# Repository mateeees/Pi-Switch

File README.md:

# Pi-Switch
## About
Pi Switch is a project that turns your Raspberry Pi into multi purpouse on/off switch for your : 
* servers
* computers
* and theoreticaly much more

## Website

https://mateeees.github.io/Pi-Switch/

## How it works?
You SSH to the Pi Switch and using the python script you turn on one of the three LEDs that shine directly to a photoresistor,which lowers its resistance to a minumum,"shorts the circuit" instead of a power switch, and turns on/off your device. 

## Simple python script:

```python
import RPi.GPIO as GPIO
import time
import sys

print("")
print('\x1b[1;35;40m' + 'SERVERS:' + '\x1b[0m')
print('\x1b[2;33;40m' + 'SERVER1 - 1' + '\x1b[0m')
print('\x1b[2;33;40m' + 'SERVER2 - 2' + '\x1b[0m')
print('\x1b[2;33;40m' + 'SERVER3 - 3' + '\x1b[0m')
val = input('\x1b[1;35;40m' + 'SERVER TO TURN ON:   ' + '\x1b[0m')
print("")
print("")

#IFs

if val == 1:
        GPIO.setmode(GPIO.BCM)
        GPIO.setwarnings(False)
        GPIO.setup(14,GPIO.OUT)
        print('\x1b[0;30;42m' + 'LED  ON' + '\x1b[0m')
        GPIO.output(14,GPIO.HIGH)
        time.sleep(2)
        print('\x1b[0;30;41m' + 'LED OFF' + '\x1b[0m')
        GPIO.output(14,GPIO.LOW)

elif val == 2:
        GPIO.setmode(GPIO.BCM)
        GPIO.setwarnings(False)
        GPIO.setup(16,GPIO.OUT)
        print('\x1b[0;30;42m' + 'LED  ON' + '\x1b[0m')
        GPIO.output(16,GPIO.HIGH)
        time.sleep(2)
        print('\x1b[0;30;41m' + 'LED OFF' + '\x1b[0m')
        GPIO.output(16,GPIO.LOW)

elif val == 3:
        GPIO.setmode(GPIO.BCM)
        GPIO.setwarnings(False)
        GPIO.setup(18,GPIO.OUT)
        print('\x1b[0;30;42m' + 'LED  ON' + '\x1b[0m')
        GPIO.output(18,GPIO.HIGH)
        time.sleep(2)
        print('\x1b[0;30;41m' + 'LED OFF' + '\x1b[0m')
        GPIO.output(18,GPIO.LOW)

else:
	print('\x1b[1;37;41m' + 'USE ONE OF THE AVIBLE OPTIONS' + '\x1b[0m')
	raw_input('\x1b[2;31;40m' + 'use any key to continue' + '\x1b[0m'
  
```

## Resources
All resources are opensource,so you can make it to! <br/>
All of these resources are specifically designed for my pourpuses,but it's really easy to change that. For the python script you can just use IDE to change that. <br/>
Something like:
```python
if val == 1:
        GPIO.setmode(GPIO.BCM)
        GPIO.setwarnings(False)
        GPIO.setup(14,GPIO.OUT)
        print('\x1b[0;30;42m' + 'LED  ON' + '\x1b[0m')
        GPIO.output(14,GPIO.HIGH)
        time.sleep(2)
        print('\x1b[0;30;41m' + 'LED OFF' + '\x1b[0m')
        GPIO.output(14,GPIO.LOW)
```
To:
```python
if val == 1:
        GPIO.setmode(GPIO.BCM)
        GPIO.setwarnings(False)
        GPIO.setup(24,GPIO.OUT)
        print('\x1b[0;30;42m' + 'LED  ON' + '\x1b[0m')
        GPIO.output(24,GPIO.HIGH)
        time.sleep(2)
        print('\x1b[0;30;41m' + 'LED OFF' + '\x1b[0m')
        GPIO.output(24,GPIO.LOW)
```
(Pins have been changed from 14 to 24) <br/> <br/>
And for the PCB you can either use an editor(i use Eagle) to edit the .BRD file and then export it to your gerber files, or you can use the lazy method. You can just use some pinhead jumper wires to connect it to the different pin.

## Build tutorial:
### LED assembly
Start with assembling three LED assemblies. It is very easy,just put photoresistor and LED into shrink tube. <br/>
You start with:

Continue with:

And finish with:

### Soldering
You will start with a PCB(i recommend the printed one) -additional tip-use pieace of masking tape to prevent scratching while using thhird arm 

And you solder everything on the top except thhe female piheaders. <br/>
Bottom:
 <br/>
Top:

## Parts list:

### Parts you will need
* 3* Photoresistor (i use the LDR5516 ).
* Switch or pinhead jumper
* Female piheaders
       <br/>-Crimping contants KONPC-SPK-PI,you can buy in bulk,they are really cheap,if you mess up.
       <br/>-Plastic shells for crimping contacts KONPC-SPK-10,buy more of them,they are cheap and you are gona ruin a few by sniping it.
       <br/>-Female 2.54mm pinhead row BL240G-V8,0,buy more of them,they are cheap and you are gona ruin a few by sniping it.
* Male piheaders
       <br/>-Female pihead row (for switch and output ) S1G26C,buy more of them,they are cheap and you are gona ruin a few by sniping it.
* 3* 100Ω Resistors
* 3* Good old 5mm white LEDs(3V)
* Connector/pihead - for output you can either use some kind of 6pin connector or just pinheads.
* PCB
       <br/>-You can either use a multi-purpouse PCB or a printed one.(Order one based on my schematics or just download the gerber .ZIP file from my Github page.)
soldering equipment
       <br/>-Soldering iron
       <br/>-Tin(I recommend >1mm),propably lead free
       <br/>-Some good flux or a soldering paste
       <br/>-Wet sponge for cleaning the soldering iron.
       <br/>-Additional soldering eqpiment like: third arm,soldering iron stand,magnifying glass.....
* Some generic cable
* And obviosuly Raspberry Pi,theoreticly you can use any of the(except pico) but i reccomend one with a ethernet port.

### Optional:

* Wire strippers
* clipers
* Breadboard for testing
* Some generic 2.54mm jumper wires
* Shrink tubes (I recomend two diametrs,one for the LED assembly,and smaller one for generic pourpuses.)

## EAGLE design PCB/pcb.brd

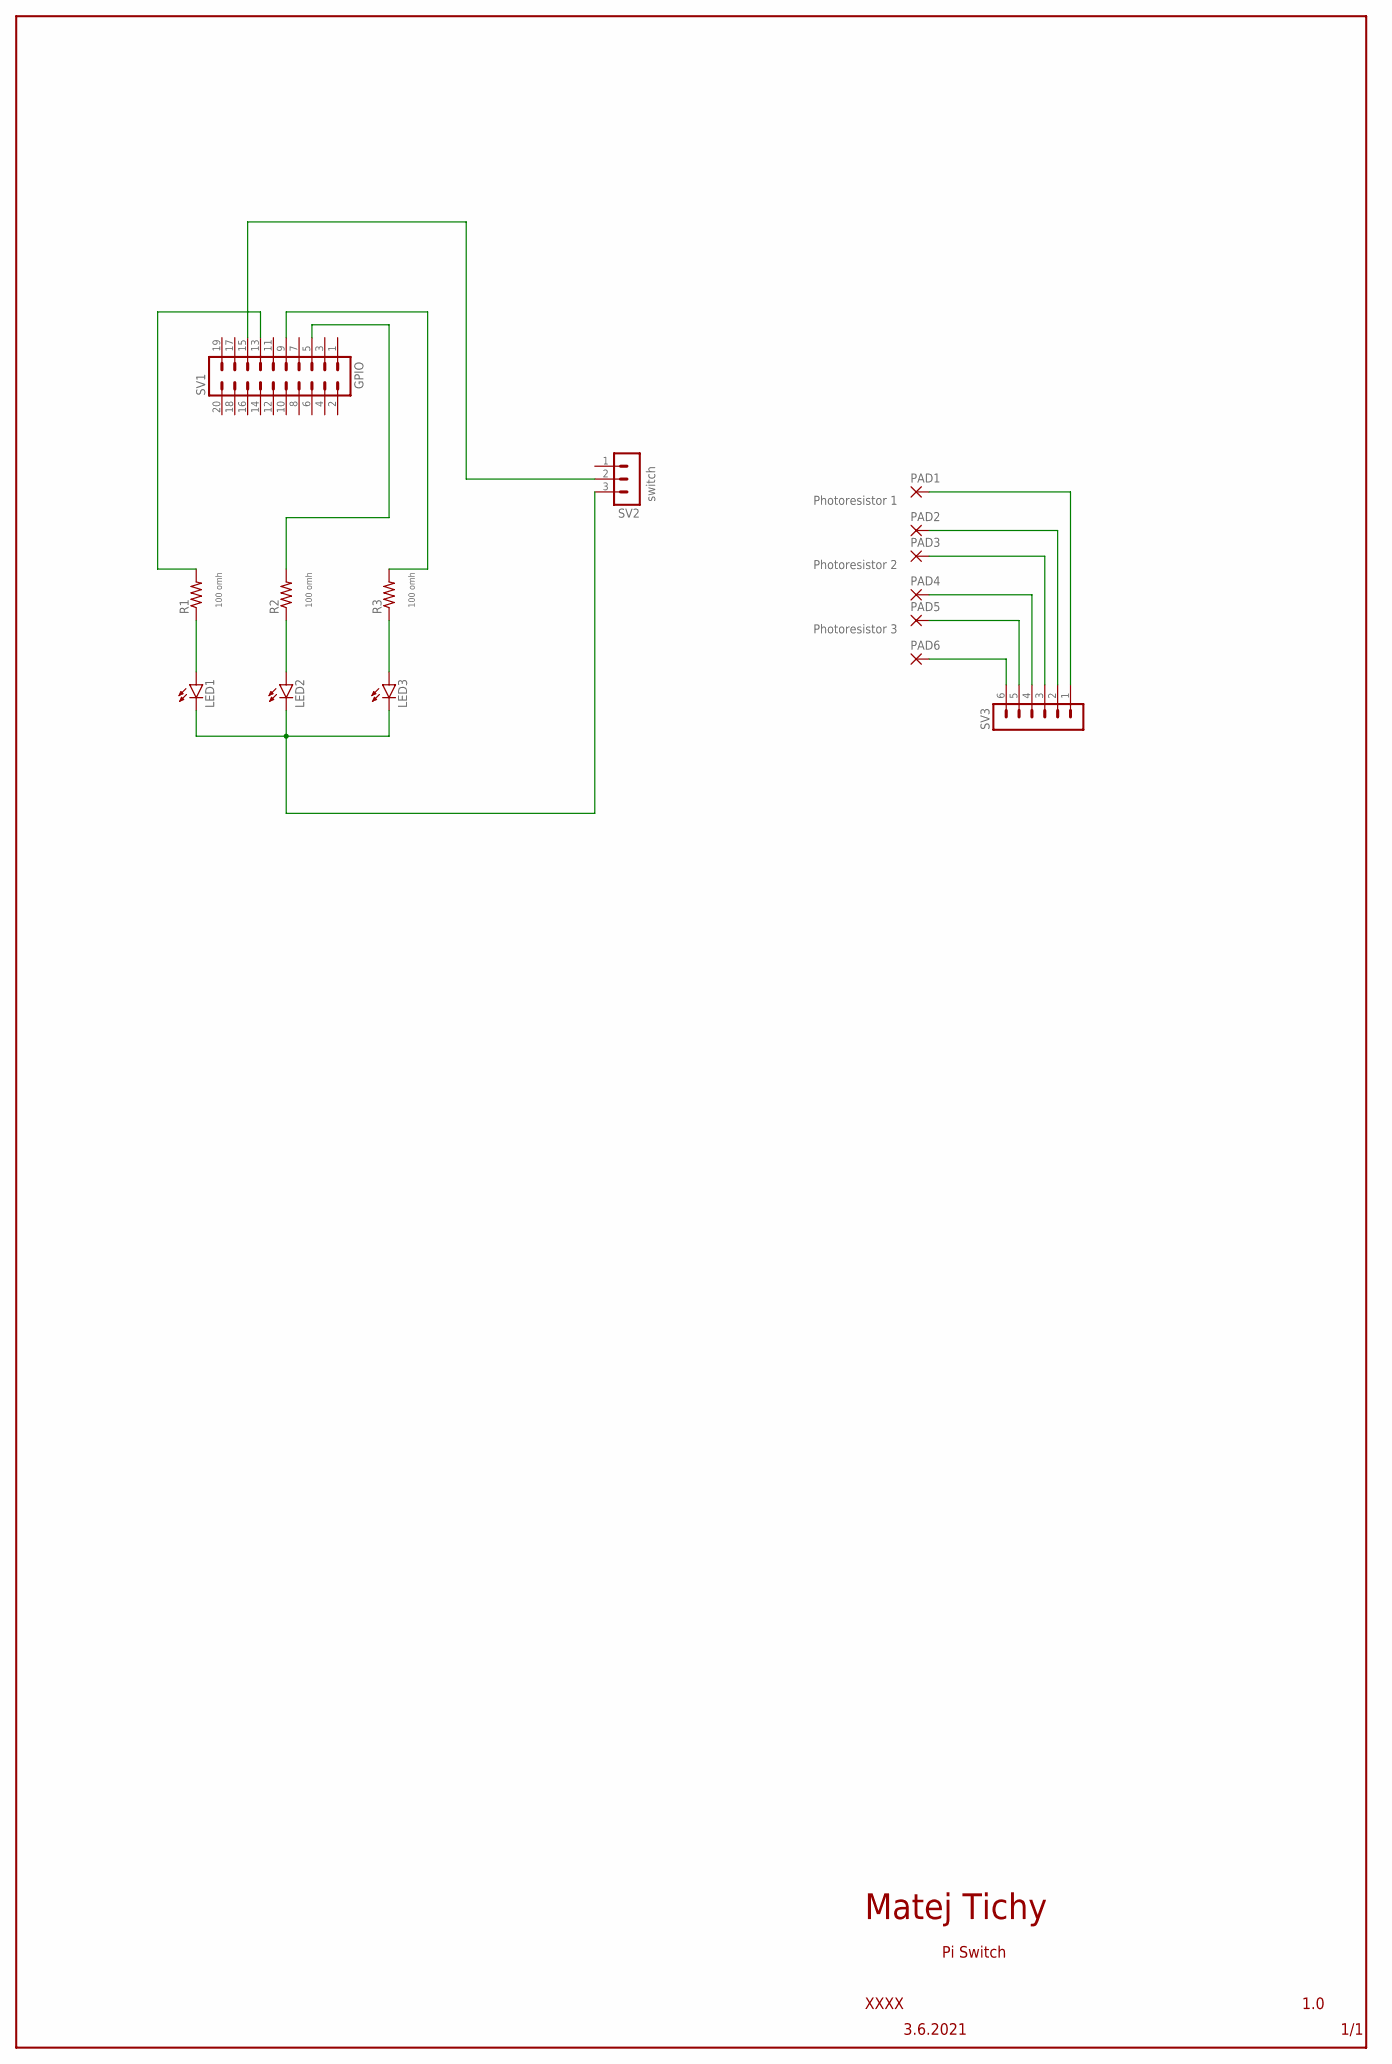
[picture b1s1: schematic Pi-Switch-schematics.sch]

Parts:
LED1, LED2, LED3: LED5MM
PAD1, PAD2, PAD3, PAD4, PAD5, PAD6: 1,6/0,8
R1, R2, R3: R-US_0204/7; 0204/7
SV1: MA10-2
SV2: MA03-1
SV3: MA06-1

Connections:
GROUND: LED1.K (C), LED2.K (C), LED3.K (C), SV2.3
unnamed: PAD6.1, SV3.6
unnamed: R2.2, SV1.5
unnamed: LED3.A, R3.1
unnamed: LED2.A, R2.1
unnamed: LED1.A, R1.1
unnamed: R1.2, SV1.13
unnamed: R3.2, SV1.9
unnamed: SV1.15, SV2.2
unnamed: PAD5.1, SV3.5
unnamed: PAD4.1, SV3.4
unnamed: PAD3.1, SV3.3
unnamed: PAD2.1, SV3.2
unnamed: PAD1.1, SV3.1

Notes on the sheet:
Pi Switch
1.0
3.6.2021
XXXX
1/1
Matej Tichy
100 omh
Photoresistor 1
Photoresistor 2
Photoresistor 3
switch
GPIO

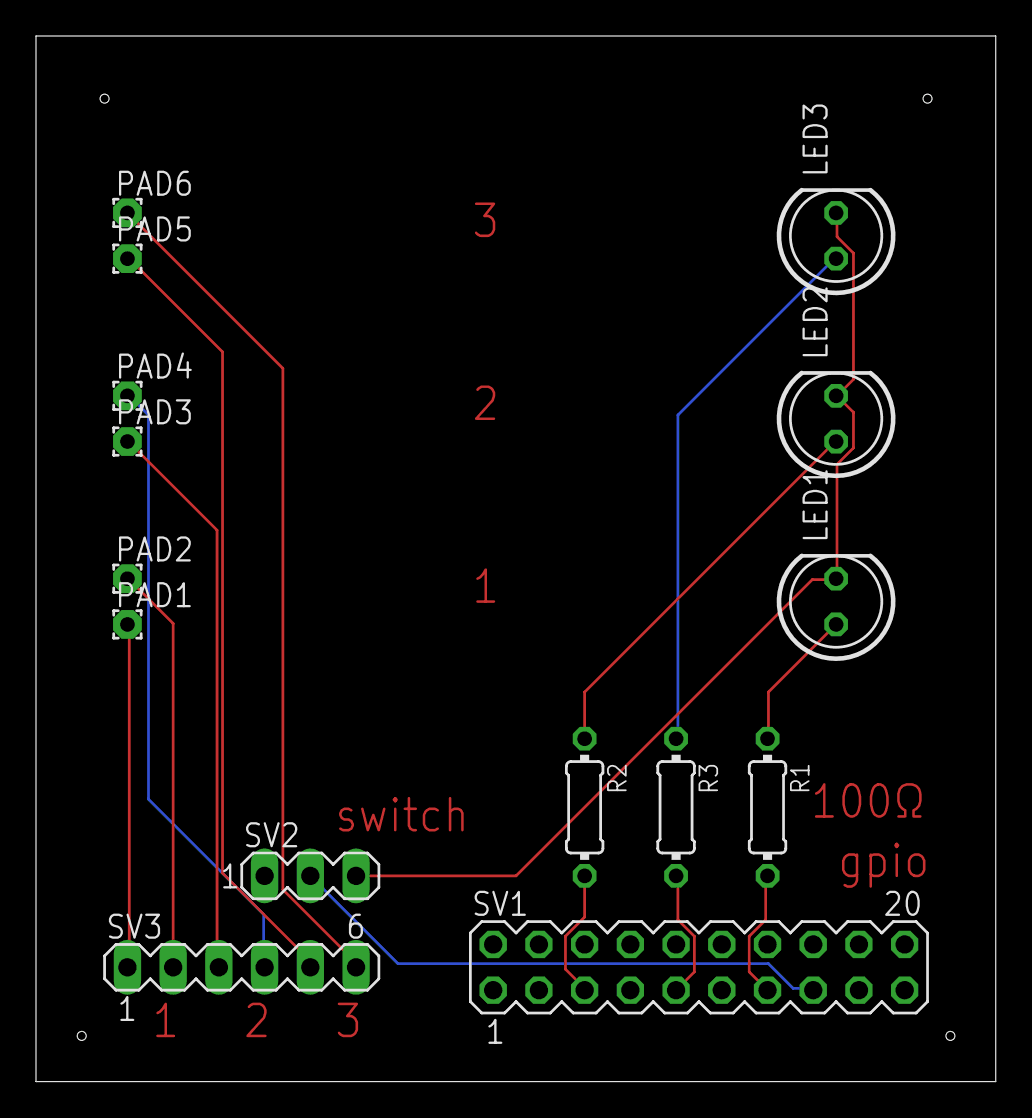
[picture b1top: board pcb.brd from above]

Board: 2 copper layers, 53.3 x 58.1 mm, 15 parts (0 on the bottom side), 14 nets.

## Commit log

2021-09-05 Rename pcb.brd to Pi-Switch-pcb.brd
2021-09-05 Rename Pi-Switch-pcb.brd to Pi-Switch-board.brd
2021-09-05 Rename PCB/pcb.sch to Pi-Switch-schematics.sch
2021-09-05 Rename Pi-Switch-schematics.sch to PCB/Pi-Switch-schematics.sch
2021-09-06 Update issue templates
2021-09-11 Create index.html
    added index for website
2021-09-13 Update README.md
    added python script to readme
